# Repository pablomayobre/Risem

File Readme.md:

# Risem

[Risem](https://positive07.github.io/Risem/) is the final school project that we (my team and I) will work on.

We go to a Technical School and in our last year in this Highschool we make a final project to show the things that we learned over the last six years.

## Team

The team is composed by three persons:

*    Gutierrez Bianchi, Mora
*    Mayobre, Pablo Ariel
*    Mazzocca, Franco Gabriel

We are all students at the ESETP N°748 in Trelew, Chubut - Argentina, in the Electronics career. We are all 17 and in our last year of highschool (2014).

## The project

The school already has a Radio Station, with a HUGE Power Supply, a [Yaesu FT-857D](http://www.yaesu.com/indexVS.cfm?cmd=DisplayProducts&ProdCatID=102&encProdID=8CBB7C4BDBAF40129AD4253A4987523C) and other equipment.

Our aim is to use this station to receive images from the [NOAA Satellites](http://www.n2yo.com/satellites/?c=4), this can be done using a [Quadrifilar Helix (QFH)](http://www.g4ilo.com/qfh.html) antenna, but we wanted to use a [Crossed Yagi-Uda antenna](http://sv1bsx.50webs.com/antenna-pol/polarization.html), this means that we need to track the satellite and aim the antenna at it.

To reach our goal we intend to create a system composed of four main parts:

+   The antenna: A simple Yagi-Uda antenna calculated at the main frequency of the NOAA satellites
+   The rotator: A stepper motor drived, two axis rotator, that enables the antenna to move in azimuth and elevation
+   The controller system: Based around PIC micro-controller from [Microchip](http://www.microchip.com/). This communicates with the PC and commands the motors in the rotator
+   The software: A software that can communicate with the PIC through USB to send the data captured from GPredict

## Gpredict

[Gpredict](http://gpredict.oz9aec.net/) is a simple but really good software that can track satellites and calculate the azimuth, elevation and doppler effect correction in real time.

Also it can send this data over a TCP/IP connection to the [Hamlib's](http://sourceforge.net/projects/hamlib/) rigctld and rotctld utilities. The [protocols](https://github.com/Positive07/Risem/tree/master/Docs) used by this two softwares is available so we can easily replace them with our own software.

## NOAA Satellites

Why NOAA Satellites? They are cool!

No reason really, this project will be left in the school so it can be used as a didactic tool. The system can work with any satellite really, you just need to replace the antenna.

## Software

As stated above the software interacts with Gpredict through a TCP connection, but it also needs to have a simple user interface, and communicate with the control board. 
To do this we decided to use [LÖVE](http://www.love2d.org/) since that is the software I'm used to. 

LÖVE doesnt provide any interface to communicate with USB peripherials by default, so in order to communicate with the PIC we coded an intermediate app in C# (Visual Studio Express 2013), this app is a TCP server which offers access to the SerialPort class in .NET Framework.
Since C#, Visual Studio and .NET Framework are not Open Source we decided to minimze the code made using it. The TCP server can be replaced for other software with the same functionality allowing to easily port this program to other platforms.

## Controller Board

The controller is a home-built PCB made around the [PIC 18F4550](http://www.microchip.com/wwwproducts/Devices.aspx?dDocName=en010300), which offers an USB connection (Simulating a serial connection), a 16x2 Character Display (Used to display additional info), 2x L297 and L298 Stepper Motor Drivers, and a MAX232 serial connection (for CAT or other serial protocol).

The PIC will be programmed using MPLAB and the C18 compiler. The PCB was designed using EAGLE CAD 6.4.0

## Rotator

This will consist of two stepper motors, one to control the azimuth of the antenna, and another one to control the elevation.

The rotor will also use 2 worm reductions (one for azimuth and the other for elevation) of 1:30 ratio, to increment the torque an precission of the rotator.

## Antenna

The antenna is not a crucial part of the project, this can be easily replaced with any antenna, so no design instructions or such will be uploaded to this repo

## License

This project is Licensed under *MIT License* and Copyrighted by Mora Gutierrez, Pablo Mayobre and Franco Mazzocca.

### Contact

Send me a mail at [pablo.a.mayobre@gmail.com](mailto:pablo.a.mayobre@gmail.com) for more info.

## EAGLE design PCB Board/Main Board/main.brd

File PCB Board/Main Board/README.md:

Main Board
==========
This is the main board of the project **RISEM**. It has many modules that allow for all the interactions that are needed. These modules are the following:

*    *USB Connection:* The main board needs to be connected to the PC in order to get the Azimuth, Elevation and Frequency.

*    *Motor Controllers:* There are two motors in an AzEl Rotor, both of them are stepper motors that need to be controlled individually, for this task the board is equiped with two L297-L298 pairs, which support steppers motors up to 2A.

*    *Serial Connection:* The frequency of the Yaesu FT-857D is corrected through the use of a Serial-CAT cable, which transforms the TTL CAT signals of the Yaesu into RS-232 USART signals, in the main board a MAX232 converts the RS-232 signals into TTL signals again, in order to connect the USART module in the PIC to the Yaesu CAT module.

*    *LCD Connection:* A requirement for this project is the use of an LCD, this project is designed to support characters displays (16x2 or 16x4) with 5x7 characters.

*    *Programming Header:* The board allows to reprogram the PIC whenever there is a firmware update through a programming header.

*    *Tension Regulator:* There is a 5V L7805 tension regulator in board. This allow to power the motors and the control board with a single supply.

*    *GPIO:* The port A was left unused, this pins are free so they can be used for future extensions.

**NOTE: The GPIO pins and the RESET buttons are hidden by the LCD Adapter, to use them they need to be connected through wires or other adapter board.**

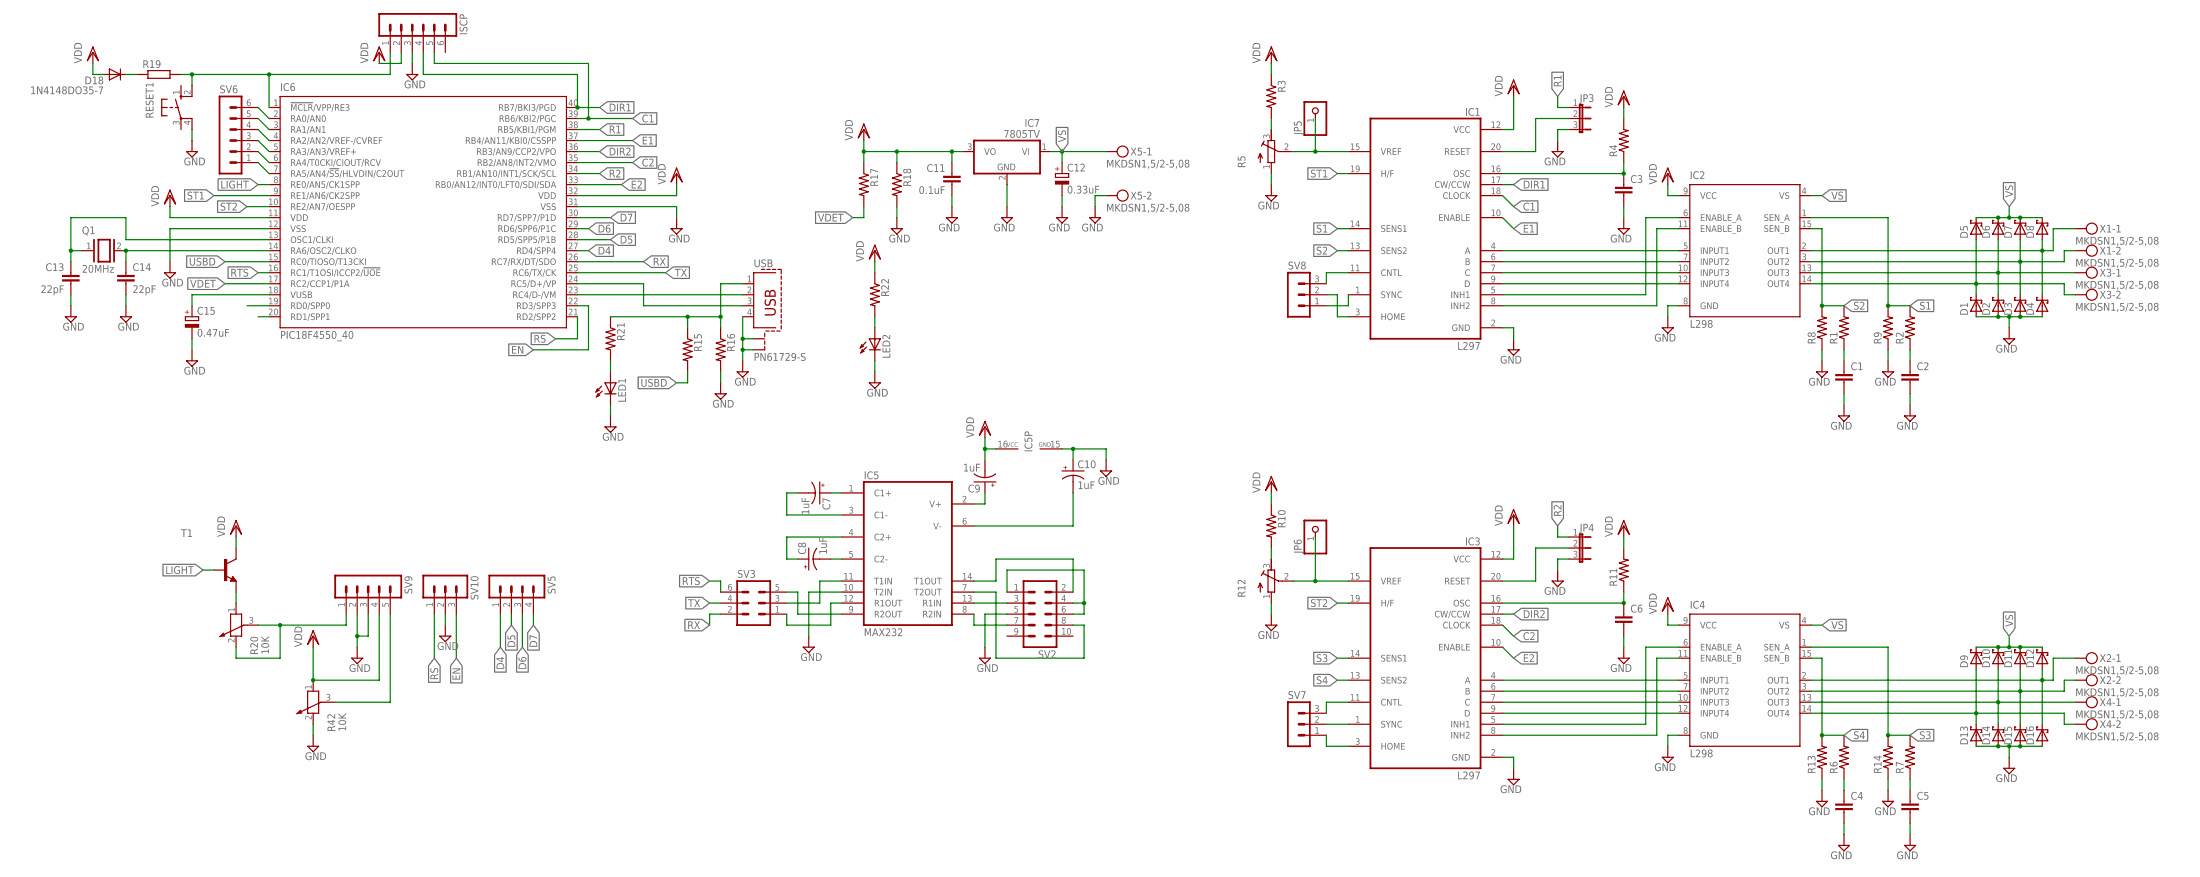
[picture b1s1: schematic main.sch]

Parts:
C1, C2, C3, C4, C5, C6: C2.5/2; C2.5-2
C7, C8, C9, C10: 1uF; E2,5-6
C11: 0.1uF; C025-025X050
C12: 0.33uF; E2,5-6
C13, C14: 22pF; C025-024X044
C15: 0.47uF; E2,5-6
D1, D2, D3, D4, D5, D6, D7, D8, D9, D10, D11, D12, D13, D14, D15, D16: SCHOTTKY-DIODEDO201T15; DO201T15
D18: 1N4148DO35-7; DO35-7
IC1, IC3: L297; DIL20
IC2, IC4: L298; MULTIWATT-15
IC5: MAX232; DIL16
IC6: PIC18F4550_40; DIL40
IC7: 7805TV; TO220V
ISCP: MA06-1
JP3, JP4: JP2E; JP2
JP5, JP6: PINHD-1X1; 1X01
LED1, LED2: LED5MM
Q1: 20MHz; QS
R1, R2, R3, R4, R6, R7, R10, R11, R15, R16, R17, R18, R21, R22: R-US_0204/7; 0204/7
R5, R12: R-TRIMM64Y; RTRIM64Y
R8, R9, R13, R14: R-US_0411/15; 0411/15
R19: R-EU_0204/7; 0204/7
R20, R42: 10K; PT-10
RESET1: 10-XX; B3F-10XX
SV2: MA05-2
SV3: MA03-2
SV5: MA04-1
SV6: MA06-1
SV7, SV8, SV10: MA03-1
SV9: MA05-1
T1: BC548-NPN-TO92-CBE; TO92-CBE
USB: PN61729-S
X1, X2, X3, X4, X5: MKDSN1,5/2-5,08

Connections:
C1: IC1.18 (CLOCK), IC6.39 (RB6/KBI2/PGC), ISCP.5
C2: IC3.18 (CLOCK), IC6.35 (RB2/AN8/INT2/VMO)
D4: IC6.27 (RD4/SPP4), SV5.1
D5: IC6.28 (RD5/SPP5/P1B), SV5.2
D6: IC6.29 (RD6/SPP6/P1C), SV5.3
D7: IC6.30 (RD7/SPP7/P1D), SV5.4
DIR1: IC1.17 (CW/CCW), IC6.40 (RB7/BKI3/PGD), ISCP.4
DIR2: IC3.17 (CW/CCW), IC6.36 (RB3/AN9/CCP2/VPO)
E1: IC1.10 (ENABLE), IC6.37 (RB4/AN11/KBI0/CSSPP)
E2: IC3.10 (ENABLE), IC6.33 (RB0/AN12/INT0/LFT0/SDI/SDA)
EN: IC6.22 (RD3/SPP3), SV10.3
GND: C1.2, C2.2, C3.2, C4.2, C5.2, C6.2, C10.+, C11.2, C12.-, C13.2, C14.2, C15.-, D1.A, D2.A, D3.A, D4.A, D13.A, D14.A, D15.A, D16.A, IC1.2 (GND), IC2.8 (GND), IC3.2 (GND), IC4.8 (GND), IC5.10 (T2IN), IC5.15 (GND), IC6.12 (VSS), IC6.31 (VSS), IC7.2 (GND), ISCP.3, JP3.3, JP4.3, LED1.K (C), LED2.K (C), R5.1 (E), R8.1, R9.1, R12.1 (E), R13.1, R14.1, R16.2, R18.2, R42.2, RESET1.4 (P1), SV2.5, SV9.2, SV9.3, SV10.2, USB.4, USB.S1, USB.S2, X5.2
LIGHT: IC6.8 (RE0/AN5/CK1SPP), T1.B
unnamed: IC1.4 (A), IC2.5 (INPUT1)
unnamed: IC1.8 (INH2), IC2.11 (ENABLE_B)
unnamed: IC1.9 (D), IC2.12 (INPUT4)
unnamed: IC1.7 (C), IC2.10 (INPUT3)
unnamed: IC1.6 (B), IC2.7 (INPUT2)
unnamed: IC1.5 (INH1), IC2.6 (ENABLE_A)
unnamed: C1.1, R1.1
unnamed: C2.1, R2.1
unnamed: IC3.9 (D), IC4.12 (INPUT4)
unnamed: IC3.7 (C), IC4.10 (INPUT3)
unnamed: D4.C, D8.A, IC2.2 (OUT1), X1.1
unnamed: D3.C, D7.A, IC2.3 (OUT2), X1.2
unnamed: D2.C, D6.A, IC2.13 (OUT3), X3.1
unnamed: D1.C, D5.A, IC2.14 (OUT4), X3.2
unnamed: R3.2, R5.3 (A)
unnamed: IC5.11 (T1IN), SV3.3
unnamed: C3.1, IC1.16 (OSC), R4.1
unnamed: IC3.6 (B), IC4.7 (INPUT2)
unnamed: IC3.4 (A), IC4.5 (INPUT1)
unnamed: IC3.8 (INH2), IC4.11 (ENABLE_B)
unnamed: IC3.5 (INH1), IC4.6 (ENABLE_A)
unnamed: C4.1, R6.1
unnamed: C5.1, R7.1
unnamed: D12.A, D16.C, IC4.2 (OUT1), X2.1
unnamed: D11.A, D15.C, IC4.3 (OUT2), X2.2
unnamed: D10.A, D14.C, IC4.13 (OUT3), X4.1
unnamed: D9.A, D13.C, IC4.14 (OUT4), X4.2
unnamed: R10.2, R12.3 (A)
unnamed: IC3.15 (VREF), JP6.1, R12.2 (S)
unnamed: C6.1, IC3.16 (OSC), R11.1
unnamed: IC5.13 (R1IN), SV2.3
unnamed: IC3.11 (CNTL), SV7.3
unnamed: IC5.9 (R2OUT), SV3.5
unnamed: IC5.12 (R1OUT), SV3.1
unnamed: R15.1, R16.1, R21.1, USB.1
unnamed: C13.1, IC6.13 (OSC1/CLKI), Q1.1
unnamed: C14.1, IC6.14 (RA6/OSC2/CLKO), Q1.2
unnamed: IC1.20 (RESET), JP3.2
unnamed: IC6.1 (!MCLR!/VPP/RE3), ISCP.1, R19.2, RESET1.2 (S1)
unnamed: D18.C, R19.1
unnamed: IC3.20 (RESET), JP4.2
unnamed: IC3.1 (SYNC), SV7.2
unnamed: IC3.3 (HOME), SV7.1
unnamed: IC1.11 (CNTL), SV8.3
unnamed: IC1.3 (HOME), SV8.2
unnamed: IC1.1 (SYNC), SV8.1
unnamed: IC6.2 (RA0/AN0), SV6.6
unnamed: R20.1, T1.E
unnamed: IC6.3 (RA1/AN1), SV6.5
unnamed: SV2.1, SV2.4, SV2.6
unnamed: R20.2, R20.3, SV9.1
unnamed: IC5.14 (T1OUT), SV2.2
unnamed: IC5.7 (T2OUT), SV2.8
unnamed: IC5.8 (R2IN), SV2.7
unnamed: IC6.4 (RA2/AN2/VREF-/CVREF), SV6.4
unnamed: IC6.5 (RA3/AN3/VREF+), SV6.3
unnamed: IC6.6 (RA4/T0CKI/CIOUT/RCV), SV6.2
unnamed: IC6.7 (RA5/AN4/!SS!/HLVDIN/C2OUT), SV6.1
unnamed: LED1.A, R21.2
unnamed: LED2.A, R22.2
unnamed: C15.+, IC6.18 (VUSB)
unnamed: IC6.23 (RC4/D-/VM), USB.2
unnamed: IC6.24 (RC5/D+/VP), USB.3
unnamed: C8.-, IC5.5 (C2-)
unnamed: IC1.15 (VREF), JP5.1, R5.2 (S)
unnamed: C8.+, IC5.4 (C2+)
unnamed: C7.+, IC5.1 (C1+)
unnamed: C7.-, IC5.3 (C1-)
unnamed: C9.+, IC5.2 (V+)
unnamed: C10.-, IC5.6 (V-)
unnamed: R42.3, SV9.5
R1: IC6.38 (RB5/KBI1/PGM), JP3.1
R2: IC6.34 (RB1/AN10/INT1/SCK/SCL), JP4.1
RS: IC6.21 (RD2/SPP2), SV10.1
RTS: IC6.16 (RC1/T1OSI/ICCP2/!UOE), SV3.6
RX: IC6.26 (RC7/RX/DT/SDO), SV3.2
S1: IC1.14 (SENS1), IC2.1 (SEN_A), R2.2, R9.2
S2: IC1.13 (SENS2), IC2.15 (SEN_B), R1.2, R8.2
S3: IC3.14 (SENS1), IC4.1 (SEN_A), R7.2, R14.2
S4: IC3.13 (SENS2), IC4.15 (SEN_B), R6.2, R13.2
ST1: IC1.19 (H/F), IC6.9 (RE1/AN6/CK2SPP)
ST2: IC3.19 (H/F), IC6.10 (RE2/AN7/OESPP)
TX: IC6.25 (RC6/TX/CK), SV3.4
USBD: IC6.15 (RC0/TIOSO/T13CKI), R15.2
VDD: C9.-, C11.1, D18.A, IC1.12 (VCC), IC2.9 (VCC), IC3.12 (VCC), IC4.9 (VCC), IC5.16 (VCC), IC6.11 (VDD), IC6.32 (VDD), IC7.3 (VO), ISCP.2, R3.1, R4.2, R10.1, R11.2, R17.1, R18.1, R22.1, R42.1, SV9.4, T1.C
VDET: IC6.17 (RC2/CCP1/P1A), R17.2
VS: C12.+, D5.C, D6.C, D7.C, D8.C, D9.C, D10.C, D11.C, D12.C, IC2.4 (VS), IC4.4 (VS), IC7.1 (VI), X5.1

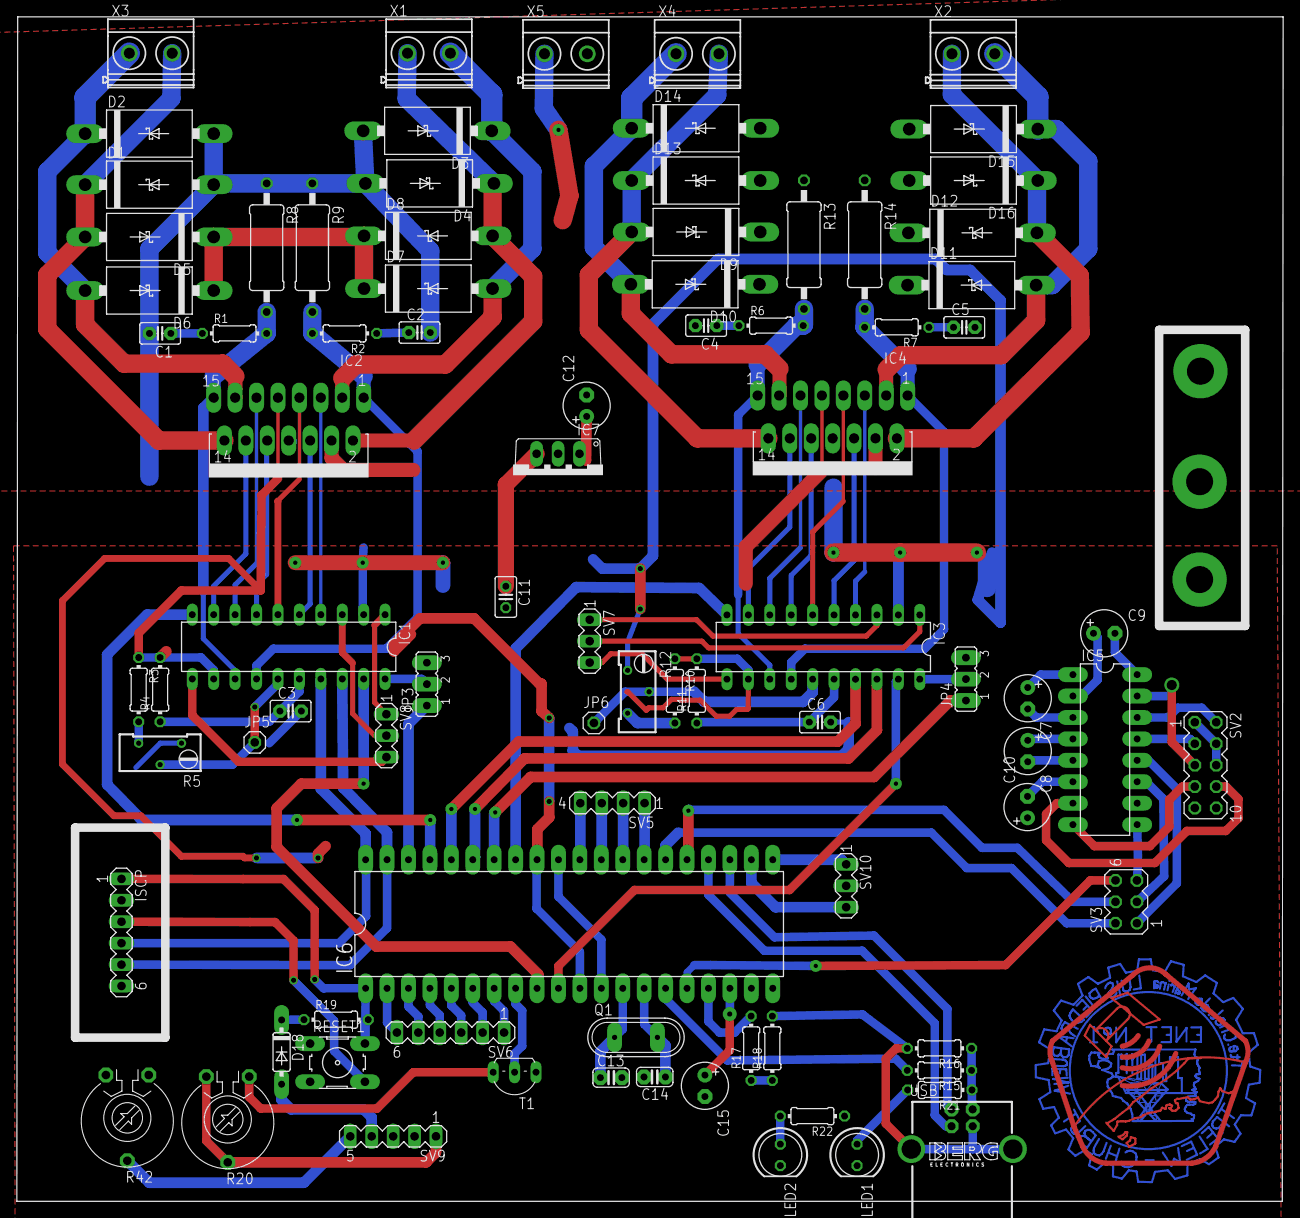
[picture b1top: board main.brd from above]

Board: 2 copper layers, 150.1 x 140.4 mm, 87 parts (0 on the bottom side), 100 nets.

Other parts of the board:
RW: LOGOENET

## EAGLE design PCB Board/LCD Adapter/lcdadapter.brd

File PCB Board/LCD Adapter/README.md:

LCD Adapter
===========
This is a PCB made for the project **RISEM**. It's used to adapt the main board LCD terminals into a single row of pins, this allows the use of a parallel (plain) cable for the connection between the LCD board and the Main board

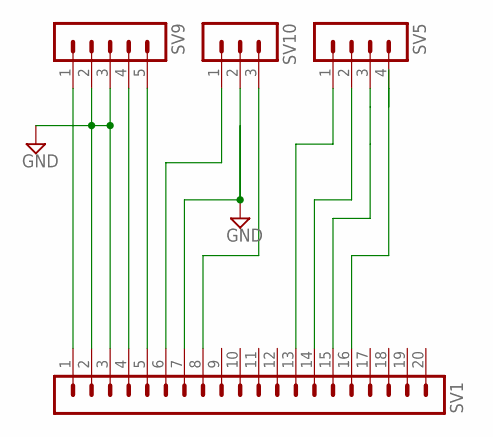
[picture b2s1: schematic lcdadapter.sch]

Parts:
SV1: MA20-1L
SV5: MA04-1
SV9: MA05-1
SV10: MA03-1

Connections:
D4: SV1.13, SV5.1
D5: SV1.14, SV5.2
D6: SV1.15, SV5.3
EN: SV1.8, SV10.3
unnamed: SV1.16, SV5.4
unnamed: SV1.4, SV9.4
unnamed: SV1.1, SV9.1
unnamed: SV1.2, SV1.3, SV1.7, SV9.2, SV9.3, SV10.2
unnamed: SV1.5, SV9.5
RS: SV1.6, SV10.1

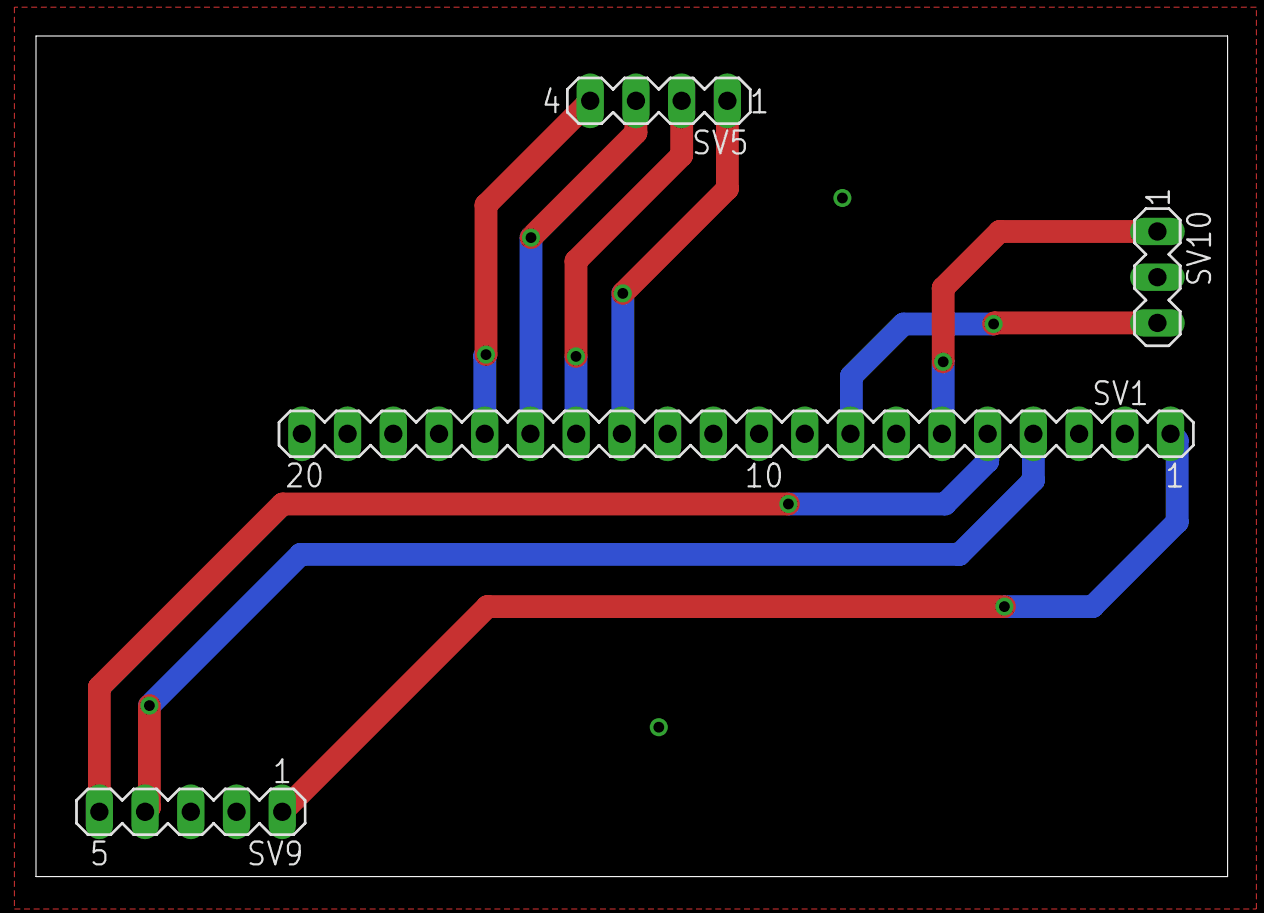
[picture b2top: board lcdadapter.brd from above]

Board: 2 copper layers, 66.2 x 46.7 mm, 4 parts (0 on the bottom side), 10 nets.

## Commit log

2014-11-01 Added PC Software
    All the PC Software developed until today (in use, discarded software
    wont be commited to this repo)
2014-11-01 Added PCB Board
    Added the PCB Boards designs, made in EAGLE CAD. This are the last
    iteration of the project
2014-11-01 Added entries to the .gitignore
2014-11-01 Main board description update
2014-11-01 LCD Adapter description update
2014-11-01 Added README
2014-11-01 Freaking Thumbs!!!
2014-11-02 Update LICENSE
2014-11-09 Create gh-pages branch via GitHub
2014-11-09 Updated readme and added docs
    The readme had some grammar mistakes so I corrected them. Also the
    hamlib wiki is down so the documentation for rotctld and rigctld cant be
    found, uploaded a copy I had in my PC
2014-11-09 Added a link to the documentation
2014-11-10 Ported dbyll repo to gh-pages branch
2014-11-10 Moved to Risem
    The main path was pointing to dbyll instead of Risem, corrected in
    config
2014-11-10 Revert "Moved to Risem"
    This reverts commit d4387f1950be82fe3b5b6f379c840288735c2d25.
2014-11-10 Fixed errors with config
2014-11-10 Trying to get the titles right
2014-11-10 Getting titles right
2014-11-10 Some changes to variables
2014-11-10 Titles
2014-11-11 Updated to lastest code
    Added serial communicaction
